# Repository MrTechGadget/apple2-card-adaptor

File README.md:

# Apple II Card Slot Adapter

This is a simple KiCad project to build an Apple II card slot riser.

It contains flipped pin male edge connector for connection with a standard female to female IDC 50 pin cable. I purchased this one https://www.aliexpress.us/item/2251832849656546.html

Al the power lines are connected; +5, +12, -12, and -5. 

Based on Renee Harke's Apple II Card Slot Riser that this is forked from.

# License

Copyright 2020 Renee Harke

Permission is hereby granted, free of charge, to any person obtaining a copy of this software and associated documentation files (the "Software"), to deal in the Software without restriction, including without limitation the rights to use, copy, modify, merge, publish, distribute, sublicense, and/or sell copies of the Software, and to permit persons to whom the Software is furnished to do so, subject to the following conditions:

The above copyright notice and this permission notice shall be included in all copies or substantial portions of the Software.

THE SOFTWARE IS PROVIDED "AS IS", WITHOUT WARRANTY OF ANY KIND, EXPRESS OR IMPLIED, INCLUDING BUT NOT LIMITED TO THE WARRANTIES OF MERCHANTABILITY, FITNESS FOR A PARTICULAR PURPOSE AND NONINFRINGEMENT. IN NO EVENT SHALL THE AUTHORS OR COPYRIGHT HOLDERS BE LIABLE FOR ANY CLAIM, DAMAGES OR OTHER LIABILITY, WHETHER IN AN ACTION OF CONTRACT, TORT OR OTHERWISE, ARISING FROM, OUT OF OR IN CONNECTION WITH THE SOFTWARE OR THE USE OR OTHER DEALINGS IN THE SOFTWARE.

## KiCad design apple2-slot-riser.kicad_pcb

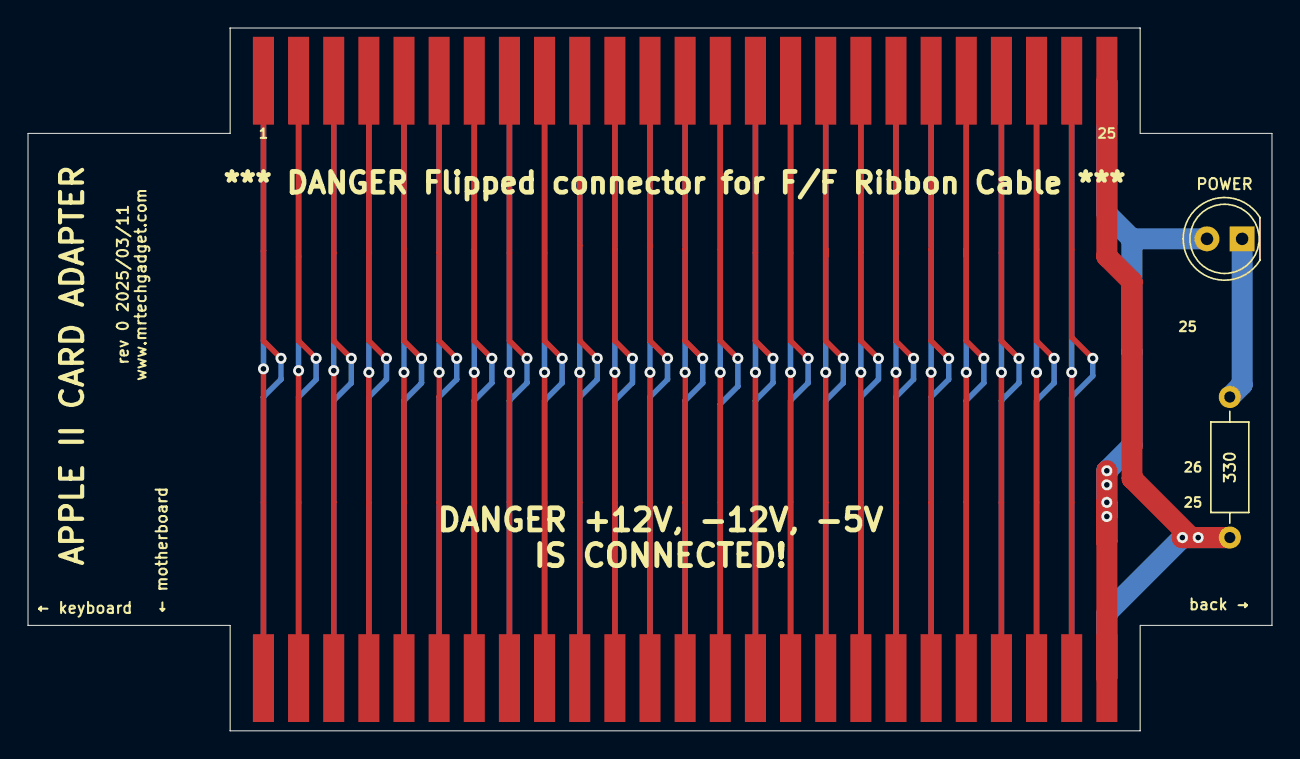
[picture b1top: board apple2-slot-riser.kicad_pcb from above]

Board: 2 copper layers, 89.9 x 50.8 mm, 4 parts (0 on the bottom side), 51 nets.

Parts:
D1: POWER; LED_D5.0mm
J1: CARD EDGE; AppleIIBus
J2: *** DANGER Flipped connector for F/F Ribbon Cable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; AppleIIBus_TightMask
R1: 330; R_Axial_DIN0207_L6.3mm_D2.5mm_P10.16mm_Horizontal

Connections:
+5V: D1.2 (A), J1.25, J2.25
-5V: J1.34, J2.34
-12V: J1.50, J2.50
/7M: J1.36, J2.36
/A0: J1.2, J2.2
/A1: J1.3, J2.3
/A2: J1.4, J2.4
/A3: J1.5, J2.5
/A4: J1.6, J2.6
/A5: J1.7, J2.7
/A6: J1.8, J2.8
/A7: J1.9, J2.9
/A8: J1.10, J2.10
/A9: J1.11, J2.11
/A10: J1.12, J2.12
/A11: J1.13, J2.13
/A12: J1.14, J2.14
/A13: J1.15, J2.15
/A14: J1.16, J2.16
/A15: J1.17, J2.17
/D0: J1.49, J2.49
/D1: J1.48, J2.48
/D2: J1.47, J2.47
/D3: J1.46, J2.46
/D4: J1.45, J2.45
/D5: J1.44, J2.44
/D6: J1.43, J2.43
/D7: J1.42, J2.42
/DEVSEL: J1.41, J2.41
/DMA: J1.22, J2.22
/DMA_IN: J1.27, J2.27
/DMA_OUT: J1.24, J2.24
/INH: J1.32, J2.32
/INT_IN: J1.28, J2.28
/INT_OUT: J1.23, J2.23
/IOSEL: J1.1, J2.1
/IOSTROBE: J1.20, J2.20
/IRQ: J1.30, J2.30
/NC19: J1.19, J2.19
/NC35: J1.35, J2.35
/NMI: J1.29, J2.29
/PHI0: J1.40, J2.40
/PHI1: J1.38, J2.38
/Q3: J1.37, J2.37
/RDY: J1.21, J2.21
/RES: J1.31, J2.31
/RW: J1.18, J2.18
/USER1: J1.39, J2.39
GND: J1.26, J2.26, R1.2
unnamed: D1.1 (K), R1.1
unnamed: J1.33, J2.33

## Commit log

2025-03-14 Add modified Kicad Files and Gerber
2025-03-14 Update Board PNG
2025-03-15 Added Ali link to cable
